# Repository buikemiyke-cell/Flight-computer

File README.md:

# Flight-computer

A flight computer with a gyroscope, barometric pressure sensor, MCU and alot of power management. It should be able to control 2 servos one for pitch and the other for yaw.

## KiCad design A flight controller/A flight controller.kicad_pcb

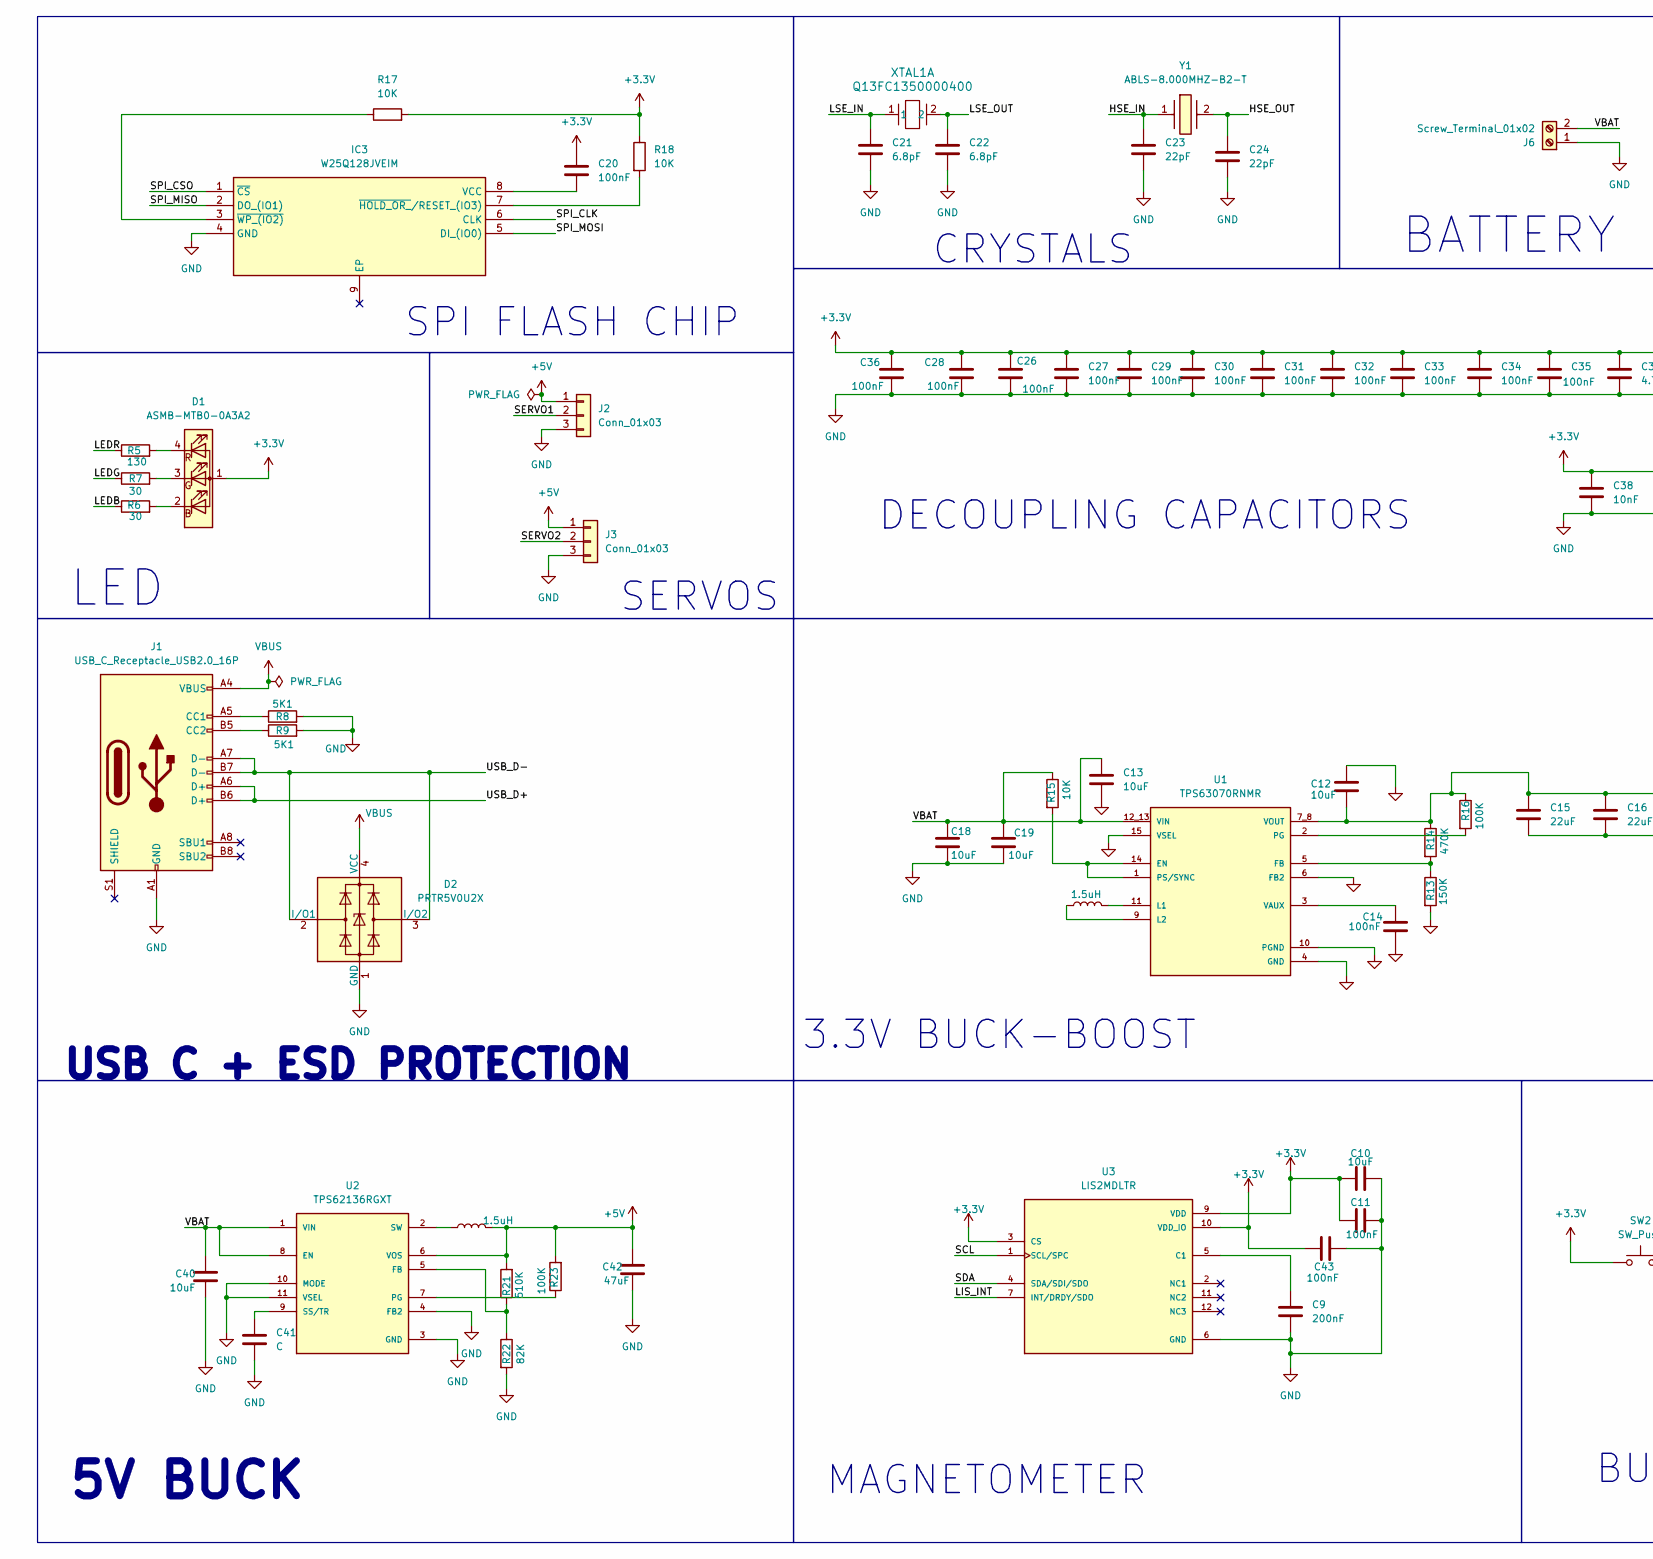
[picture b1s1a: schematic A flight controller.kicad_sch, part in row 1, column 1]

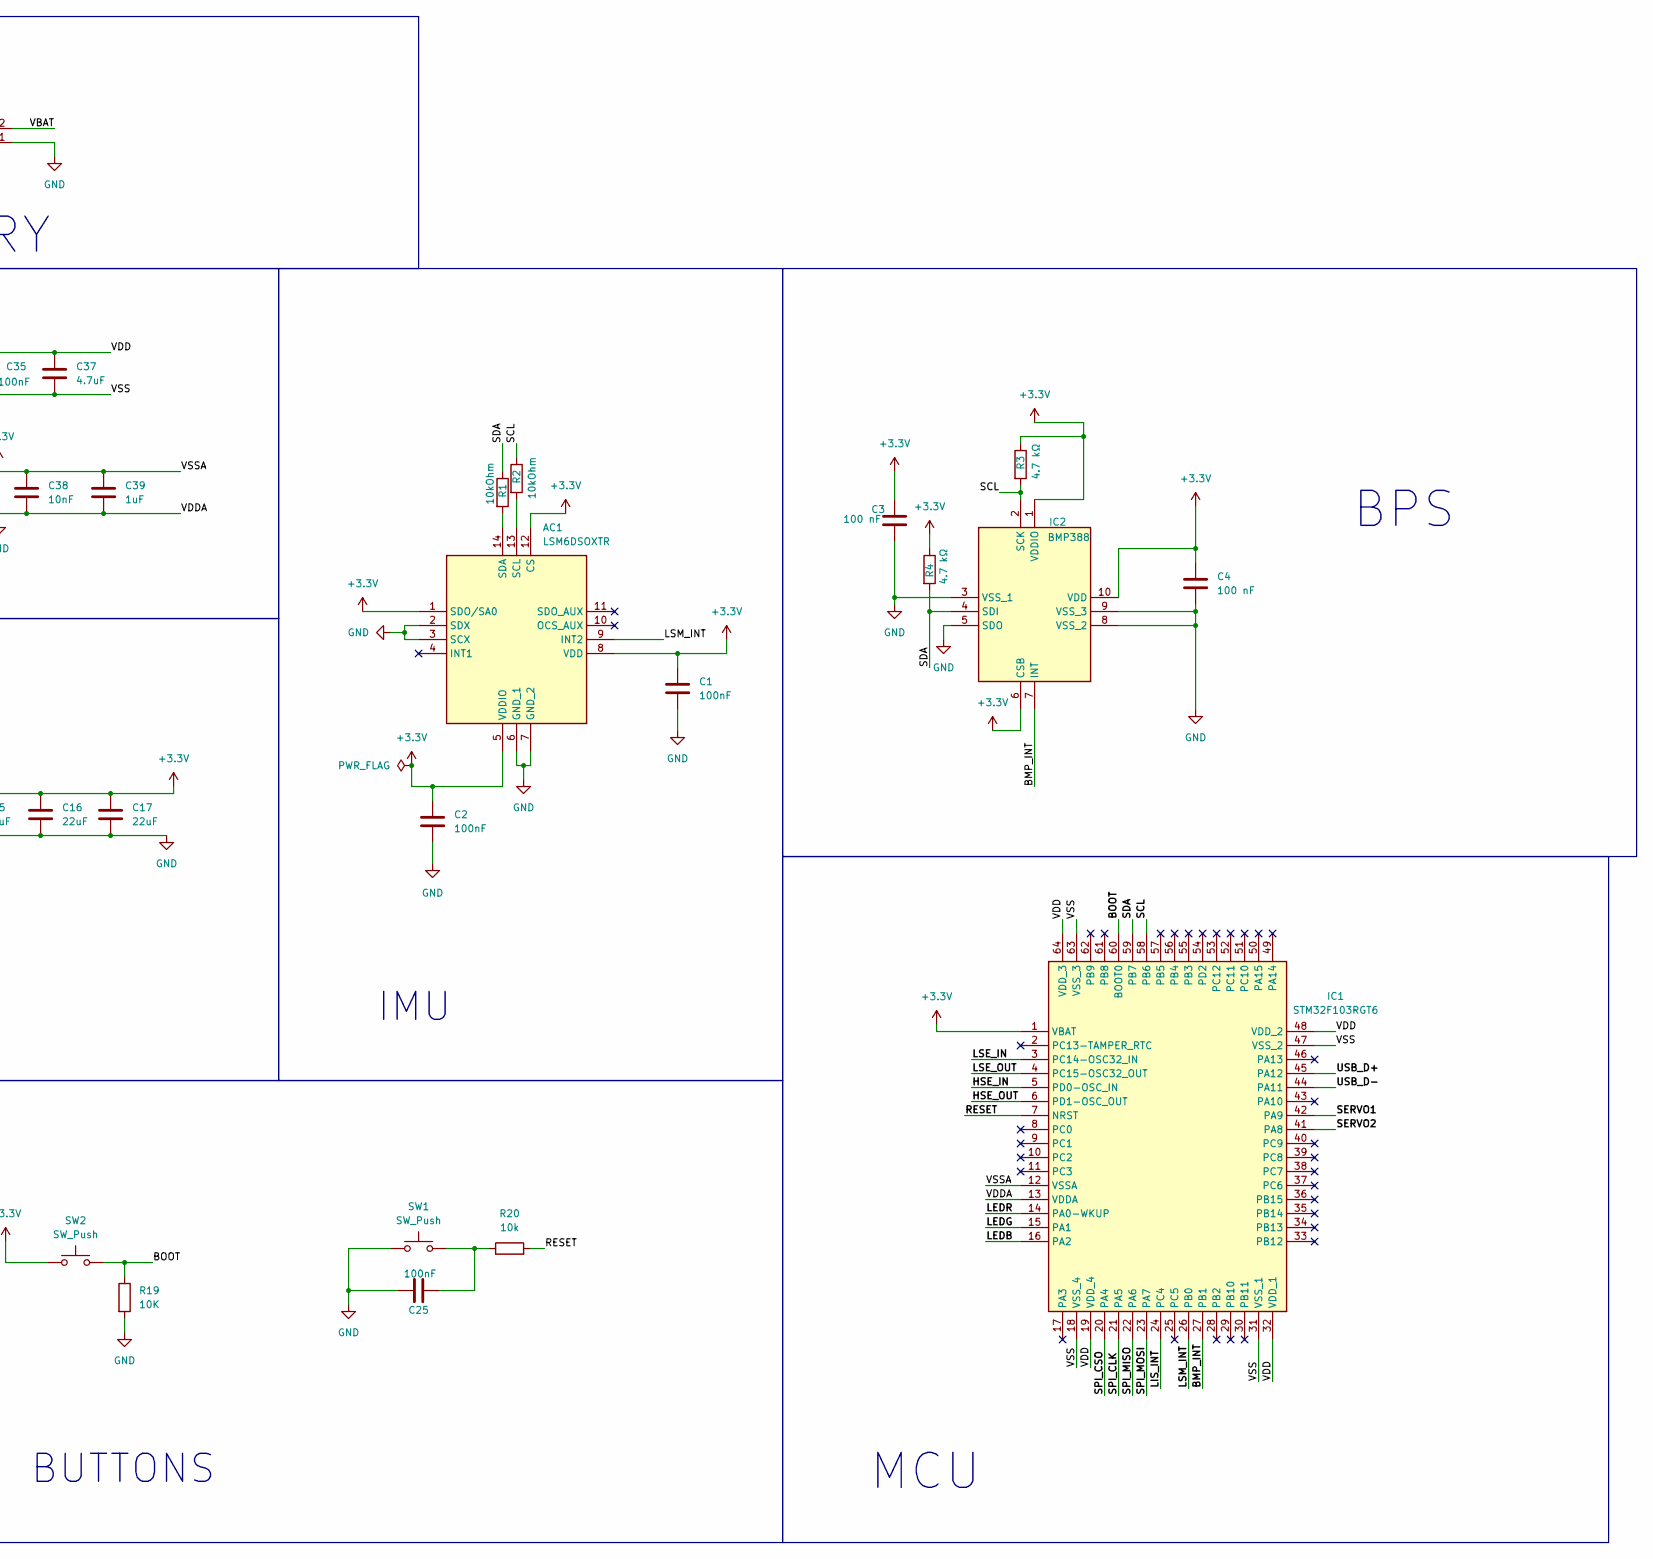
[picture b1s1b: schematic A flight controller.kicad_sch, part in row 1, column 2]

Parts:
AC1: LSM6DSOXTR; LGA-14_1; Manufacturer_Part_Number LSM6DSOXTR; Mouser Part Number 511-LSM6DSOXTR
C1, C2, C11, C14, C20, C25, C26, C27, C28, C29, C30, C31, C32, C33, C34, C35, C36, C43: 100nF; C_0402_1005Metric
C3, C4: 100 nF; C_0402_1005Metric
C9: 200nF; C_0402_1005Metric
C10, C12, C13, C18, C19, C40: 10uF; C_0402_1005Metric
C15, C16, C17: 22uF; C_0402_1005Metric
C21, C22: 6.8pF; C_0402_1005Metric
C23, C24: 22pF; C_0402_1005Metric
C37: 4.7uF; C_0402_1005Metric
C38: 10nF; C_0402_1005Metric
C39: 1uF; C_0402_1005Metric
C41: C; C_0402_1005Metric
C42: 47uF; C_0805_2012Metric
D1: ASMB-MTB0-0A3A2; LED_Avago_PLCC4_3.2x2.8mm_CW
D2: PRTR5V0U2X; SOT-143
IC1: STM32F103RGT6; QFP50P1200X1200X160-64N; Manufacturer_Part_Number STM32F103RGT6; Mouser Part Number 511-STM32F103RGT6
IC2: BMP388; Manufacturer_Part_Number BMP388
IC3: W25Q128JVEIM; SON127P800X600X80-9N-D; Mouser Part Number 454-W25Q128JVEIM
J1: USB_C_Receptacle_USB2.0_16P; USB_C_Receptacle_HCTL_HC-TYPE-C-16P-01A
J2, J3: Conn_01x03; PinHeader_1x03_P2.54mm_Vertical
J6: Screw_Terminal_01x02; TerminalBlock_Xinya_XY308-2.54-2P_1x02_P2.54mm_Horizontal
L2, L3: 1.5uH; IND_XFL4020-152MEC
R1, R2: 10kOhm; R_0201_0603Metric
R3, R4: 4.7 kΩ; R_0201_0603Metric
R5: 130; R_0201_0603Metric
R6, R7: 30; R_0201_0603Metric
R8, R9: 5K1; R_0201_0603Metric
R13: 150K; R_0201_0603Metric
R14: 470K; R_0201_0603Metric
R15, R17, R18, R19: 10K; R_0201_0603Metric
R16, R23: 100K; R_0402_1005Metric
R20: 10k; R_0201_0603Metric
R21: 510K; R_0402_1005Metric
R22: 82K; R_0402_1005Metric
SW1, SW2: SW_Push; TS1088AR02016
U1: TPS63070RNMR; VREG_TPS63070RNMR; PARTREV B
U2: TPS62136RGXT; VREG_TPS62136RGXT; PARTREV March 2017
U3: LIS2MDLTR; PQFN50P200X200X70-12N; PARTREV Rev 5
XTAL1: Q13FC1350000400; XTAL_FC-135_EPS
Y1: ABLS-8.000MHZ-B2-T; ABLS8000MHZB2T; Manufacturer_Part_Number ABLS-8.000MHZ-B2-T; Mouser Part Number 815-ABLS-8-B2

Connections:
+3.3V: AC1.1 (SDO/SA0), AC1.5 (VDDIO), AC1.8 (VDD), AC1.12 (CS), C1.1, C2.1, C3.1, C4.1, C10.1, C11.1, C12.2, C15.1, C16.1, C17.1, C20.1, C26.1, C27.1, C28.1, C29.1, C30.1, C31.1, C32.1, C33.1, C34.1, C35.1, C36.1, C37.1, C38.1, C39.1, C43.1, D1.1 (A), IC1.1 (VBAT), IC1.12 (VSSA), IC1.19 (VDD_4), IC1.32 (VDD_1), IC1.48 (VDD_2), IC1.64 (VDD_3), IC2.1 (VDDIO), IC2.6 (CSB), IC2.10 (VDD), R3.1, R4.1, R14.1, R16.1, R17.2, R18.1, SW2.1, U1.7_8 (VOUT), U3.3 (CS), U3.9 (VDD), U3.10 (VDD_IO)
+5V: C42.1, J2.1, J3.1, L3.2, R21.2, R23.2, U2.6 (VOS)
/BMP_INT: IC1.27 (PB1), IC2.7 (INT)
/BOOT: IC1.60 (BOOT0), R19.1, SW2.2
/HSE_IN: C23.1, IC1.5 (PD0-OSC_IN), Y1.1
/HSE_OUT: C24.1, IC1.6 (PD1-OSC_OUT), Y1.2
/LEDB: IC1.16 (PA2), R6.1
/LEDG: IC1.15 (PA1), R7.1
/LEDR: IC1.14 (PA0-WKUP), R5.1
/LIS_INT: IC1.24 (PC4), U3.7 (INT/DRDY/SDO)
/LSE_IN: C21.1, IC1.3 (PC14-OSC32_IN), XTAL1.1
/LSE_OUT: C22.1, IC1.4 (PC15-OSC32_OUT), XTAL1.2
/LSM_INT: AC1.9 (INT2), IC1.26 (PB0)
/RESET: IC1.7 (NRST), R20.2
/SCL: IC1.58 (PB6), IC2.2 (SCK), R2.1, R3.2, U3.1 (SCL/SPC)
/SDA: IC1.59 (PB7), IC2.4 (SDI), R1.1, R4.2, U3.4 (SDA/SDI/SDO)
/SERVO1: IC1.42 (PA9), J2.2
/SERVO2: IC1.41 (PA8), J3.2
/SPI_CLK: IC1.21 (PA5), IC3.6 (CLK)
/SPI_CSO: IC1.20 (PA4), IC3.1 (~CS)
/SPI_MISO: IC1.22 (PA6), IC3.2 (DO_(IO1))
/SPI_MOSI: IC1.23 (PA7), IC3.5 (DI_(IO0))
/USB_D+: IC1.45 (PA12), J1.A6 (D+), J1.B6 (D+)
/USB_D-: D2.2 (I/O1), D2.3 (I/O2), IC1.44 (PA11), J1.A7 (D-), J1.B7 (D-)
/VBAT: C13.1, C18.1, C19.1, C40.1, J6.2, R15.1, U1.12_13 (VIN), U2.1 (VIN), U2.8 (EN)
GND: AC1.2 (SDX), AC1.3 (SCX), AC1.6 (GND_1), AC1.7 (GND_2), C1.2, C2.2, C3.2, C4.2, C9.2, C10.2, C11.2, C12.1, C13.2, C14.2, C15.2, C16.2, C17.2, C18.2, C19.2, C21.2, C22.2, C23.2, C24.2, C25.1, C26.2, C27.2, C28.2, C29.2, C30.2, C31.2, C32.2, C33.2, C34.2, C35.2, C36.2, C37.2, C38.2, C39.2, C40.2, C41.2, C42.2, C43.2, D2.1 (GND), IC1.13 (VDDA), IC1.18 (VSS_4), IC1.31 (VSS_1), IC1.47 (VSS_2), IC1.63 (VSS_3), IC2.3 (VSS_1), IC2.5 (SDO), IC2.8 (VSS_2), IC2.9 (VSS_3), IC3.4 (GND), J1.A1 (GND), J1.A12 (GND), J1.B1 (GND), J1.B12 (GND), J2.3, J3.3, J6.1, R8.2, R9.2, R13.2, R19.2, R22.2, SW1.1, U1.4 (GND), U1.6 (FB2), U1.10 (PGND), U1.15 (VSEL), U2.3 (GND), U2.4 (FB2), U2.10 (MODE), U2.11 (VSEL), U3.6 (GND), U3.8 (GND)
unnamed: AC1.13 (SCL), R2.2
unnamed: AC1.14 (SDA), R1.2
unnamed: C25.2, R20.1, SW1.2
unnamed: D1.2 (BK), R6.2
unnamed: D1.3 (GK), R7.2
unnamed: D1.4 (RK), R5.2
unnamed: C20.2, IC3.8 (VCC)
unnamed: IC3.7 (~HOLD_OR_/RESET_(IO3)), R18.2
unnamed: IC3.3 (~WP_(IO2)), R17.1
unnamed: J1.A5 (CC1), R8.1
unnamed: J1.B5 (CC2), R9.1
unnamed: R15.2, U1.1 (PS/SYNC), U1.14 (EN)
unnamed: R13.1, R14.2, U1.5 (FB)
unnamed: L2.2, U1.11 (L1)
unnamed: L2.1, U1.9 (L2)
unnamed: R16.2, U1.2 (PG)
unnamed: C14.1, U1.3 (VAUX)
unnamed: R21.1, R22.1, U2.5 (FB)
unnamed: R23.1, U2.7 (PG)
unnamed: C41.1, U2.9 (SS/TR)
unnamed: L3.1, U2.2 (SW)
unnamed: C9.1, U3.5 (C1)
VBUS: D2.4 (VCC), J1.A4 (VBUS), J1.A9 (VBUS), J1.B4 (VBUS), J1.B9 (VBUS)

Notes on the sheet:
USB C + ESD PROTECTION
SPI FLASH CHIP
BUTTONS
5V BUCK
LED
MCU
BATTERY
3.3V BUCK-BOOST
BPS
MAGNETOMETER
SERVOS
IMU
CRYSTALS
DECOUPLING CAPACITORS

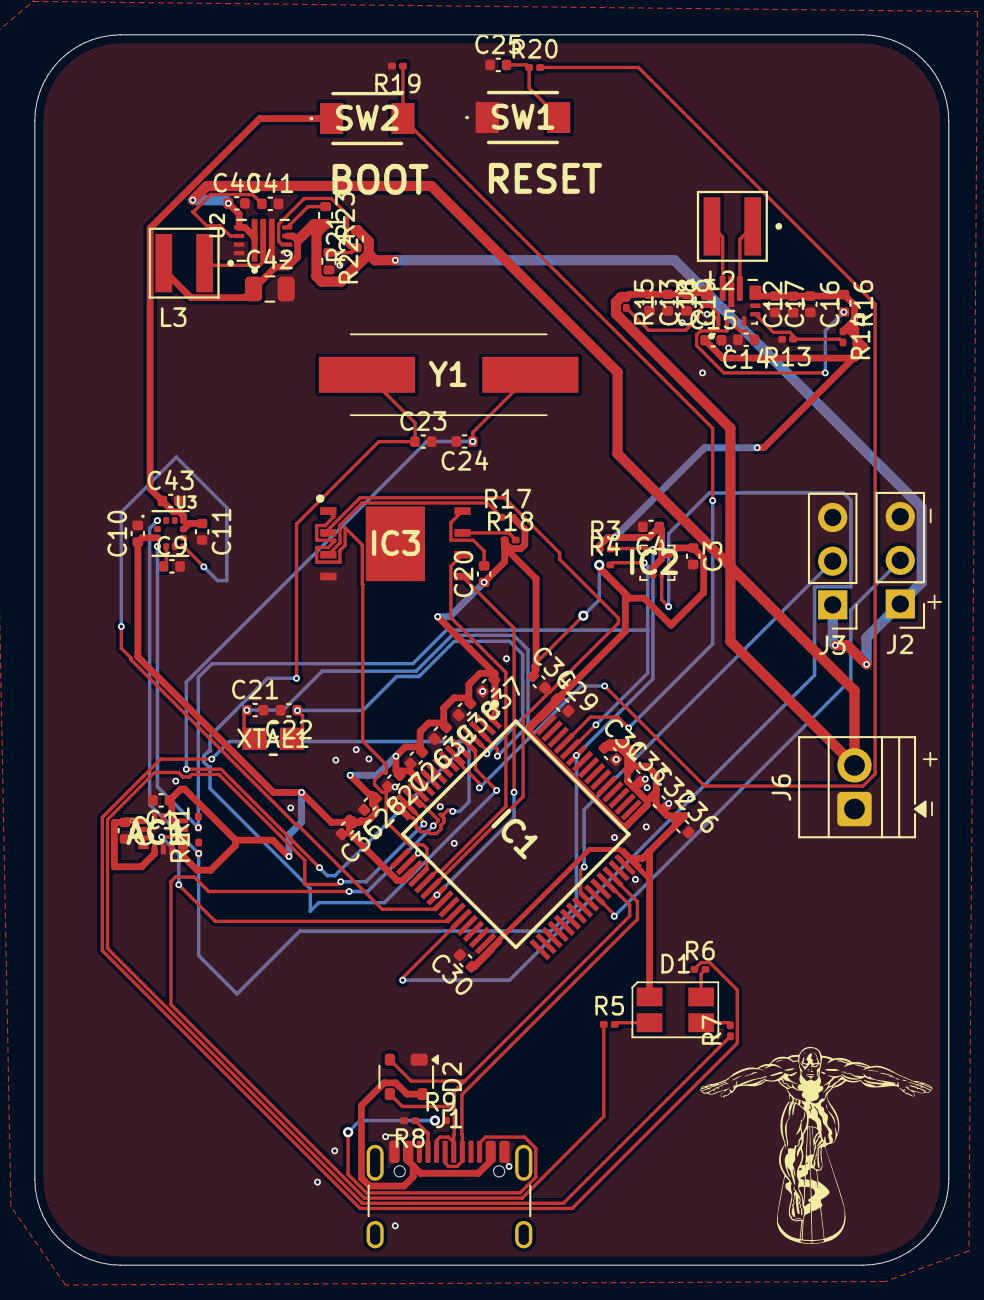
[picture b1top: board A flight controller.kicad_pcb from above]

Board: 2 copper layers, 53.2 x 71.5 mm, 78 parts (0 on the bottom side), 49 nets.

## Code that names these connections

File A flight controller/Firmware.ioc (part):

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Mcu.Name=STM32F103R(F-G)Tx
Mcu.Package=LQFP64
Mcu.UserName=STM32F103RGTx
PA0-WKUP.Signal=S_TIM2_CH1_ETR
PA1.Signal=S_TIM2_CH2
PA11.Mode=Device
PA11.Signal=USB_DM
PA12.Mode=Device
PA12.Signal=USB_DP
PA2.Signal=S_TIM2_CH3
PA4.GPIOParameters=GPIO_Label
PA4.GPIO_Label=W25_CS0
PA4.Signal=GPIO_Output
PA5.Mode=Full_Duplex_Master
PA5.Signal=SPI1_SCK
PA6.Mode=Full_Duplex_Master
PA6.Signal=SPI1_MISO
PA7.Mode=Full_Duplex_Master
PA7.Signal=SPI1_MOSI
PA8.Signal=S_TIM1_CH1
PA9.Signal=S_TIM1_CH2
PB0.GPIOParameters=GPIO_Label
PB0.GPIO_Label=LSM_INT
PB0.Signal=GPXTI0
PB1.GPIOParameters=GPIO_Label
PB1.GPIO_Label=BMP_INT
PB1.Signal=GPXTI1
PB6.Mode=I2C
PB6.Signal=I2C1_SCL
PB7.Mode=I2C
PB7.Signal=I2C1_SDA
PC14-OSC32_IN.Mode=LSE-External-Oscillator
PC14-OSC32_IN.Signal=RCC_OSC32_IN
PC15-OSC32_OUT.Mode=LSE-External-Oscillator
PC15-OSC32_OUT.Signal=RCC_OSC32_OUT
PC4.GPIOParameters=GPIO_Label
PC4.GPIO_Label=LIS_INT
PC4.Signal=GPXTI4
PD0-OSC_IN.Mode=HSE-External-Oscillator
PD0-OSC_IN.Signal=RCC_OSC_IN
PD1-OSC_OUT.Mode=HSE-External-Oscillator
PD1-OSC_OUT.Signal=RCC_OSC_OUT
RCC.SYSCLKFreq_VALUE=72000000
RCC.SYSCLKSource=RCC_SYSCLKSOURCE_PLLCLK
board=custom
